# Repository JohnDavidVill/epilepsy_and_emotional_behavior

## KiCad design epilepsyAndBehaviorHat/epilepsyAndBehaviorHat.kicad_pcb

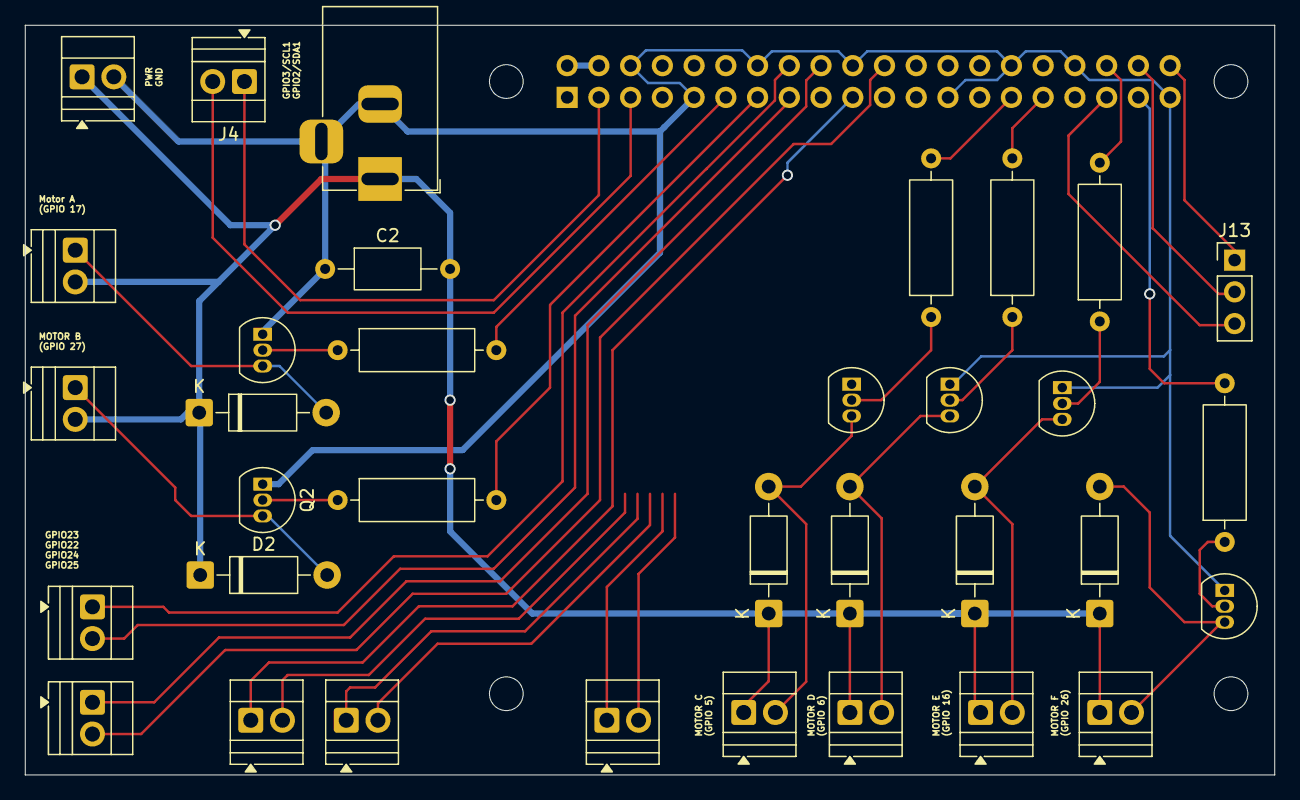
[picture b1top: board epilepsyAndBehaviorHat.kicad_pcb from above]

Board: 2 copper layers, 100.0 x 60.0 mm, 39 parts (1 on the bottom side), 32 nets.

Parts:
C2: 0.1 uF; C_Axial_L5.1mm_D3.1mm_P10.00mm_Horizontal
D1, D2, D3, D4, D5, D6: 1N4001; D_DO-41_SOD81_P10.16mm_Horizontal
J1: GPIO; PinSocket_2x20_P2.54mm_Vertical
J2: Barrel_Jack_Switch_Pin3Ring; BarrelJack_Horizontal
J3, J4, J5, J6, J7, J8, J9, J10, J11, J12, J14, J15, J16: Screw_Terminal_01x02; TerminalBlock_Xinya_XY308-2.54-2P_1x02_P2.54mm_Horizontal
J13: Conn_01x03_Pin; PinHeader_1x03_P2.54mm_Vertical
MH1, MH2, MH3, MH4: MountingHole_2.7mm_M2.5
Q1, Q2, Q3, Q4, Q5, Q6: PN2222A; TO-92_Inline
R3, R4, R5, R6, R7, R8: 220-330; R_Axial_DIN0309_L9.0mm_D3.2mm_P12.70mm_Horizontal

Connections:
+3V3: J1.1, J1.17
+5V: J1.2, J1.4
/GPIO2/SDA1: J1.3, J4.1
/GPIO3/SCL1: J1.5, J4.2
/GPIO5: J1.29, R8.2
/GPIO6: J1.31, R7.2
/GPIO10/SPI0.MOSI: J1.19, J14.1 (Pin_1_1)
/GPIO16: J1.36, R6.2
/GPIO17: J1.11, R3.2
/GPIO19/PCM.FS: J1.35, J13.3
/GPIO20/PCM.DIN: J1.38, J13.2
/GPIO21/PCM.DOUT: J1.40, J13.1
/GPIO22: J1.15, J11.2
/GPIO23: J1.16, J11.1
/GPIO24: J1.18, J12.1
/GPIO25: J1.22, J12.2
/GPIO26: J1.37, R5.2
/GPIO27: J1.13, R4.2
/PWR: C2.2, D1.1 (K), D2.1 (K), D3.1 (K), D4.1 (K), D5.1 (K), D6.1 (K), J2.1, J3.2, J5.2, J6.1, J7.1, J8.1, J9.1, J10.1
GND: C2.1, J1.6, J1.9, J1.14, J1.20, J1.25, J1.30, J1.34, J1.39, J2.2, J2.3, J10.2, Q1.1 (E), Q2.1 (E), Q3.1 (E), Q4.1 (E), Q5.1 (E), Q6.1 (E)
unnamed: D1.2 (A), J3.1, Q1.3 (C)
unnamed: D2.2 (A), J5.1, Q2.3 (C)
unnamed: D3.2 (A), J6.2, Q3.3 (C)
unnamed: D4.2 (A), J7.2, Q4.3 (C)
unnamed: D5.2 (A), J8.2, Q5.3 (C)
unnamed: D6.2 (A), J9.2, Q6.3 (C)
unnamed: Q1.2 (B), R3.1
unnamed: Q2.2 (B), R4.1
unnamed: Q3.2 (B), R5.1
unnamed: Q4.2 (B), R6.1
unnamed: Q5.2 (B), R7.1
unnamed: Q6.2 (B), R8.1
